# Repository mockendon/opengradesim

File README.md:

# opengradesim
  Original Author: OpenGradeSimulator by Matt Ockendon 2019.11.14. See https://github.com/mockendon/opengradesim
  This branch by Brian Palmer 2020.4.6 at https://github.com/BrianFrankPalmer/opengradesim

  "This is the controller for a 3D printed elevation or 'grade' simulator to use with an indoor trainer.
  The project in inspired by the Wahoo Kickr Climb but shares none of its underpinnings.
  Elevation is simulated on an indoor trainer by increasing resistance over that generated by frictional
  losses." - Matt Odendon

  I was inspired to build Matt Odendon's cool opengradesim project and ended up coming up with this branch
  in the process. This version addresses a couple issues on his to-do list and adds a few other nicities.

  - A manual mode was added. Pressing the up or down button switches to manual mode. Pressing the stop button returns to smart trainer mode.
  - The blocking motor control routine was replaced with a PID controller. Now the loop() runs uninterrupted allowing the target grade
  to be constantly adjusted. This allows for accurate grade simulations (if your not peddling).
  - Peddle vibration injecting unwanted noise into the control loop was handled by locking the position once a target grade
  is achieved. It's only unlocked when the REQUESTED grade has changed by n% or more. The requested grade comes from either manual input,
  Matt's calculated grade routine,  or serial console input (+, -) during debugging/testing. But does not include the Nano's noisy sensor incline data.
  So you can now shift your weight, peddle, bang on your bike, etc. and the climber wont move unless the requested grade changes.
  - A bicolor LED was added. It turns red when the the actuator is moving and green when its locked on a target grade.
  - Now allows for negative grades.
  - Added a climber leveling mode. This mode both physically levels the bike to 0% incline and sets the controller grade display to 0%. 
  While in this mode, the up and down buttons are used adjust the bikes incline. Once you have leveled the trainer, pressing
  the stop button stores the current incline to flash memory. This value is used to automatically re-level
  the bike the next time gradeSim is started. So now you dont have to physically move the control head to level the climber and the control
  head can be mounted at an angle.

  - Added UI Setting menu that allows setting:
      Units: (imperial/metric)
      Rider/Bike Weight: combined bike/rider weight in kg or lbs
      Wheel Size: defaults to 2070 mm
      Manual Step %: Controls sensivity of manual incline/decline buttons.
      Grade Accuracy: Controls precision of grade adjustments. 
      Leveling Mode: Controls when the leveling mode is entered (each time GradeSim is started or first time only).
      PID parameters: All setting of motor control loop parameters.
      Debug Mode: When On, allows input through Serial console. 
  
  - Finished Matt's work on storage of user settings. This could easily be expanded store multiple rider/bike profiles.
  - Added a battery level display that displays the battery level of the <CABLE> device.
  - Added a IMU temperature display.  This can be used to ensure your arduino isnt overheating in its case. This was achieved by 
  upgrading to the LSM6DS3 driver. See https://github.com/arduino-libraries/Arduino_LSM6DS3/issues/9. Uncomment the display lines to use.

  The circuit: This is basically like Matt's circuit except -
  - I use a bigger actuator that requires a bigger motor driver. After experementing with a few different boards I ended up using a
  Sabertooth 3x32 that I had from a previous project. They are pricey, but worth it. It can be controlled with 3V signal eliminating the
  need for a logic level shifter, can be controlled with just two wires, and COMPLETELY ELIMINATED THE MOTOR WHINE AT ALL SPEEDS.
  Update - this was a bad idea. The sabertooth is really designed to be powered by a battery or a PSU. I couldnt get it to run for more than a
  few minutes off a wall wart, so I am using a 12 V PSU.
  - Uses a 3 button pad instead of 2.
  - Added a bi-color LED to indicate state.
  - Added 3 POTS for storing initial PID param values. I ended up not using these for anything because the PID values are stored in ROM and can
  be be adjusted in Settings -> PID values.
  - Uses a Serial cable connector between the control box and the motor driver. I had planned to swap this out for a coiled 6-pin RJ-12 cable.
  But after tripping over the serial cable a few times without causing any damage, I think I will stick with it.

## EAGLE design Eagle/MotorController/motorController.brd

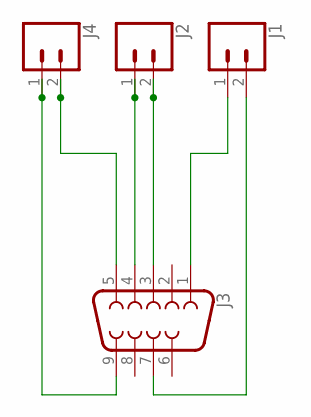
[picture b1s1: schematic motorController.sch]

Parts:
J1, J2, J4: CONN_025MM; SCREWTERMINAL-5MM-2
J3: DB9FEMALE; DB9

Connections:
unnamed: J2.2, J3.3
unnamed: J1.2, J3.7
unnamed: J2.1, J3.4
unnamed: J1.1, J3.1
unnamed: J3.5, J4.2
unnamed: J3.9, J4.1

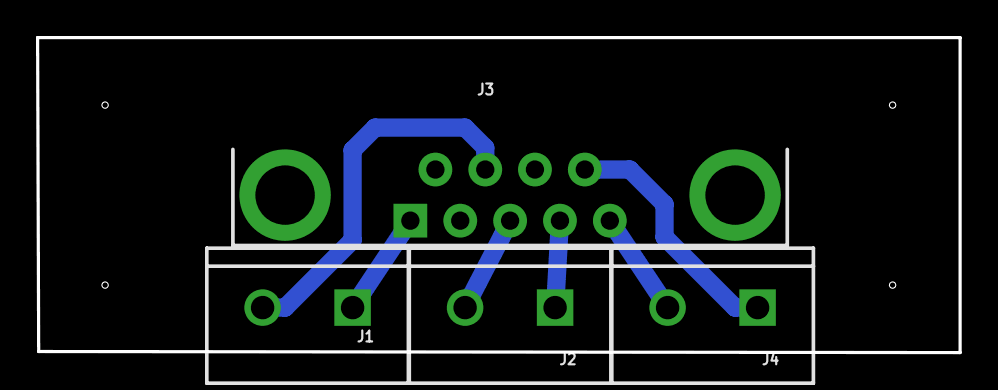
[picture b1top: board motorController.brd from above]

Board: 2 copper layers, 51.2 x 17.5 mm, 4 parts (0 on the bottom side), 6 nets.

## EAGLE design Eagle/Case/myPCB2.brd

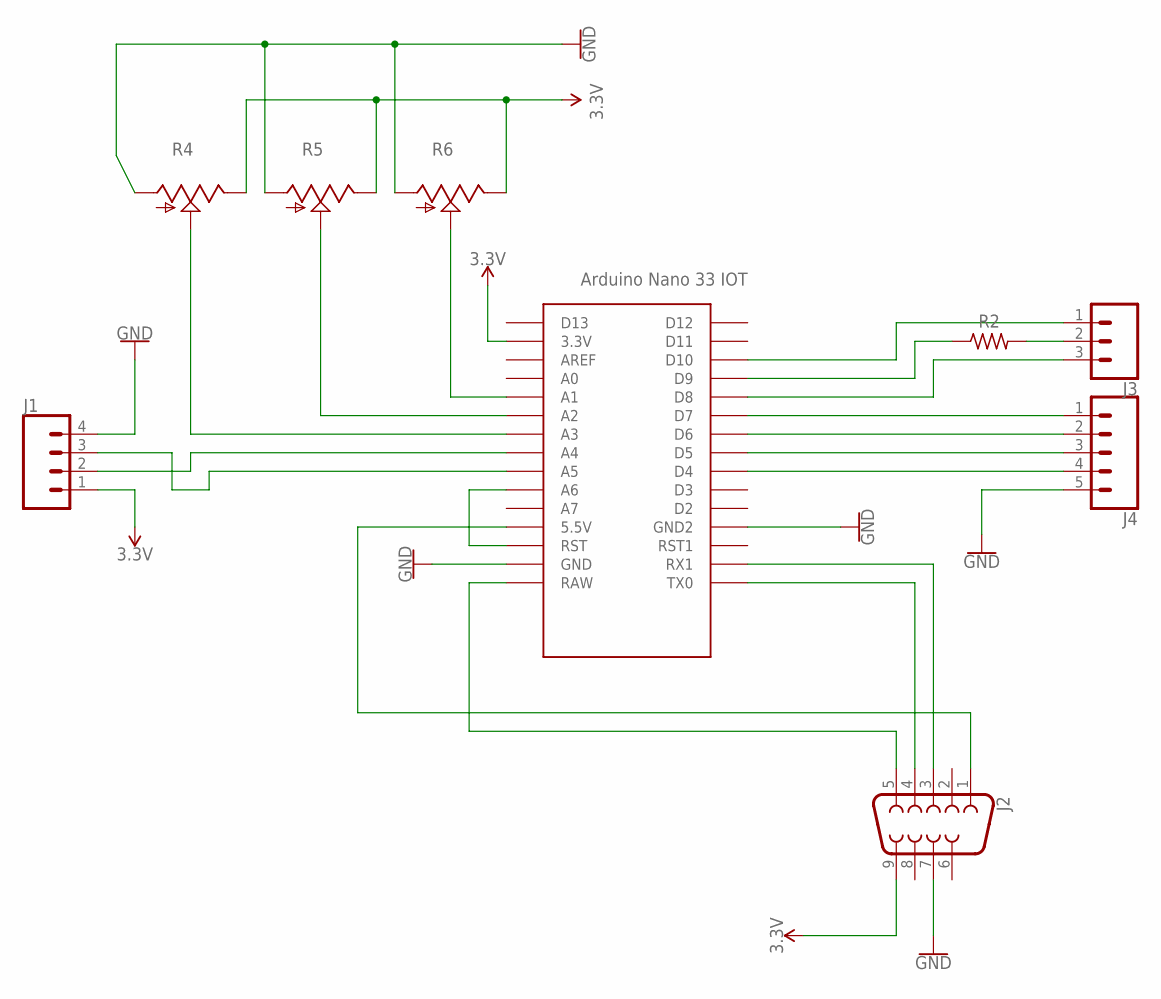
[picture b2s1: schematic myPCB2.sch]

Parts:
J1: CONN_04; 1X04
J2: DB9FEMALE; DB9
J3: CONN_03; 1X03
J4: CONN_05; 1X05
R2: R-US_AXIAL-7.2MM-PITCH; RESAD724W46L381D178B
R4, R5, R6: TRIM_US-S63P; S63P
U$2: NANO33IOT

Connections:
3.3V: J1.1, J2.9, R4.E, R5.E, R6.E, U$2.3.3V
GND: J1.4, J2.7, J4.5, R4.A, R5.A, R6.A, U$2.GND, U$2.GND1 (GND2)
unnamed: J2.3, U$2.RX1
unnamed: J3.3, U$2.D8
unnamed: J4.3, U$2.D5
unnamed: J4.4, U$2.D4
unnamed: J1.2, U$2.A4
unnamed: J2.4, U$2.TX0
unnamed: J1.3, U$2.A5
unnamed: J2.5, U$2.RAW
unnamed: J2.1, U$2.5V (5.5V)
unnamed: R2.1, U$2.D9
unnamed: U$2.A6, U$2.RST
unnamed: J4.1, U$2.D7
unnamed: J3.1, U$2.D10
unnamed: R6.S, U$2.A1
unnamed: R5.S, U$2.A2
unnamed: R4.S, U$2.A3
unnamed: J4.2, U$2.D6
unnamed: J3.2, R2.2

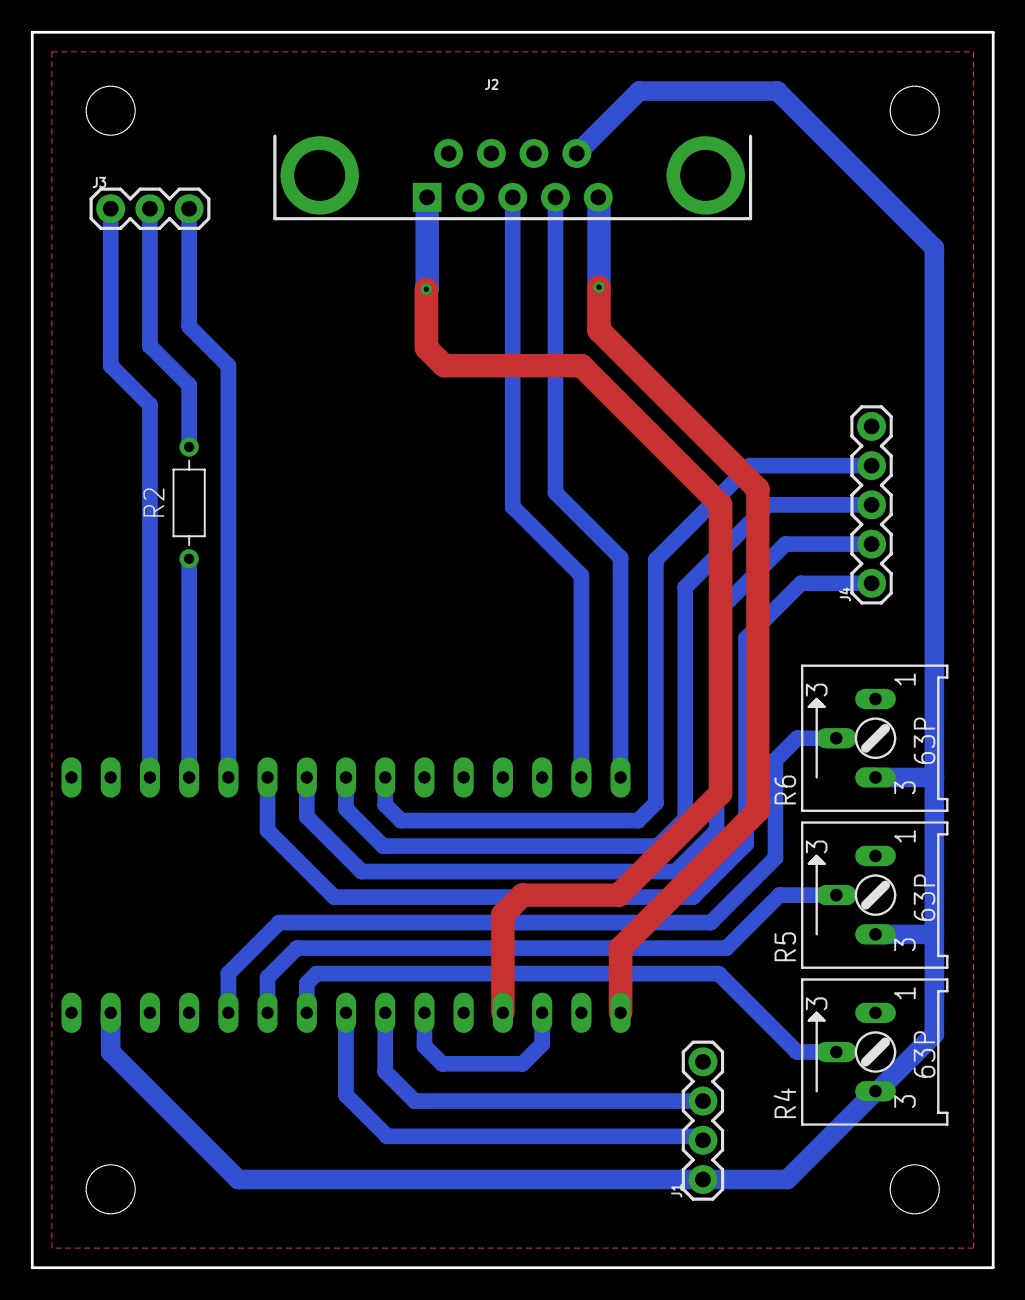
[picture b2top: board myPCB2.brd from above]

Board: 2 copper layers, 62.2 x 80.0 mm, 9 parts (0 on the bottom side), 20 nets.

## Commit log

2019-11-18 Add files via upload
    First release version
2019-11-23 Add files via upload
    Version 1.01, Considered the first release version. Tweaked some parameters esp moving average set sizes on speed and power and the frequency of incline changes. Rotated the display to suit the mark 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
2020-07-13 Initital Commit
    Initial commit of my version of mokendon's awsome OpenGradeSim. This is a work in progress.
    I've aded:
    - classes for menus, OLED display, and buttons.
    - auto-leveling of control unit
    - ability to change wheel size
    - ability to change weight settings at anytime
2020-07-14 misc
    Code cleanup, added a debug mode to menu that can be switched on and off, now forces auto-leveleling when entering smart trainer mode if needed, converted blocking delay in refreshSpeedandPower to us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
2020-07-14 misc cleanup
    display ble scanning msg just once
2020-07-15 manual and smartTrainer modes merged
    - Pressing an up or down button flips to manual mode immediately. Pressing the select button switches back to smart trainer mode.
    - fixed bugs in setNumber and setDouble. Less is more.
    - misc refactoring
2020-07-15 Update OpenGradeSim.ino
    bug fix preventing displaying negative grades.
2020-07-16 bug fixes
    fixing up down button defines and bug in pressAnyButtonToExit
2020-07-23 sorting out trainer leveling
    sorting out trainer leveling
2020-07-31 Update OpenGradeSim.ino
    Added second pid setting used when trainter is close to target. This really sorted it the jittering issue.
2020-08-01 updated readme
    updated readme and some other misc;
2020-08-20 First fully working version.
    Combined the trainer leveling and smartTrainer mode code into gradeSim method.
    turned off debug mode.
2020-08-21 moveActuator
    update moveActuator to not calculate pwm when target grade is achieved.
2020-08-24 Fixed the issue with peddling vibration
    - Fixed the issue with peddling vibration being constantly injected into the control loop. It now locks the targetGrade until it is changed by manual input or the smart trainer.
    - Changed trainerIncline from an int to a double for finer grain control.
    - Debug mode now recieves innput from serial monitor. + and - modifies target grade by .25 degress.
2020-08-27 rounds targetgrade input to an int.
    - now rounds targetgrade input to an int.
2020-08-31 updating fcomments mostly
    updting comments mostly.
2020-09-05 fixed reset system bug
    Fixed the reset system issue by updating the pin # from 19 to 20.
    some other minor refactoring and comments.
2020-09-05 updated readme
    updated readme
2020-09-05 Update README.md
    updated readme
2020-09-12 Added Eagle files for PCB, 3d Modesl of Case, Screen shots of pcb and case.
    Added Eagle PCB files.
    EAGLE Schematic and PCB Screenshots.
    Added 3d models of Controller Case and Bike Mount
2020-09-12 added eagle motor controller files
    added eagle motor controller files
2021-01-01 work on moveActuator
    took off the 1% change in incline limiter.
    now adust the P PID param dynamically. Allows for faster seeking of target grade when error is large.
2021-01-01 added >Cable device battery level display
    now subscribes the >Cable device battery service and displays it on the Grad Sim display.
2021-01-02 improved display of BLE service data
    - Gradsim mode: Improved handling of ble service data in first line.
2021-01-12 Version 1.04
    Version 1.04
    - converted Matts getBLEServices() to non blocking code. This allows the UI to stay active while waiting for ble to connect to the trainer.
    -Now stores the UUID of thge cable device so we scan reconnect with BLE.scanForUuid
    -improved formatting of decimal numbers.
    -added battery level of Cable Device to UI
2021-04-18 work in progress
    version 1.05
    -Added Set Unit option to display in imperial or metric. Affects speed and weight.
    - improved menu handling of non-numeric menu option.
    - added option to adjust "Manual Step %". This controls the step size when in GradeSim manual mode.
    This controls how sensitive the hunt and seek grade routine is. Default is .05%.
    - added min/max range checking for gui input
2021-04-18 Revert "work in progress"
    This reverts commit bc20cb5175af6a1f98239cb17f67179c61a7ee16.
2021-04-25 v 1.05
    lets try this again. v 1.05
2021-04-30 Version 1.06
    - Fixed a bug when reading speed updates that reduced the resolution by half.
    - Fixed a bug not allowing Speed to return to zero.
    - Switched to using BLE.EventHandler
    - Added disconnect / reconnect handling
2021-04-30 Update README.md
    update readme
2021-04-30 v 1.07
    v 1.07
    Added new Level/Ride option to the main menu. This allows quick override of the user prefs to force a quick leveling cycle.
    Some misc refactoring for readability.
2021-05-15 Update OpenGradeSim.ino
    added debug options:
    P = increase power
    p = decrease power
    S = increase speed
    s = decrease speed
    Other misc refactoring
2021-05-19 moving stuff around
    moving stuff around

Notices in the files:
parts and their libraries:
SparkFun-Connectors: Licensing: Creative Commons ShareAlike 4.0 International - https://creativecommons.org/licenses/by-sa/4.0
